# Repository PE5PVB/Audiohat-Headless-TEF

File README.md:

# Audiohat for Headless TEF

This is an add-on PCB for the Headless TEF, it will provide an extra analog audio output.

## Contributing
I'm open for a new ideas in our project. Feel free to share your thoughts in [Discussions](https://github.com/PE5PVB/Audiohat-Headless-TEF/discussions).\
You can also contribute to the project using [Pull Requests](https://github.com/PE5PVB/Audiohat-Headless-TEF/pulls). We will review it and merge into main branch.

You are using my hardware and you found a difficulty? Please create new [issue](https://github.com/PE5PVB/Audiohat-Headless-TEF/issues) and describe your problem.

I also would like to invite you to join our Discord community where we share our ideas and help each other with some issues.\

Special thanks to all [contributors](https://github.com/PE5PVB/Audiohat-Headless-TEF/graphs/contributors). You are awesome! ❤️

## If you like this hardware

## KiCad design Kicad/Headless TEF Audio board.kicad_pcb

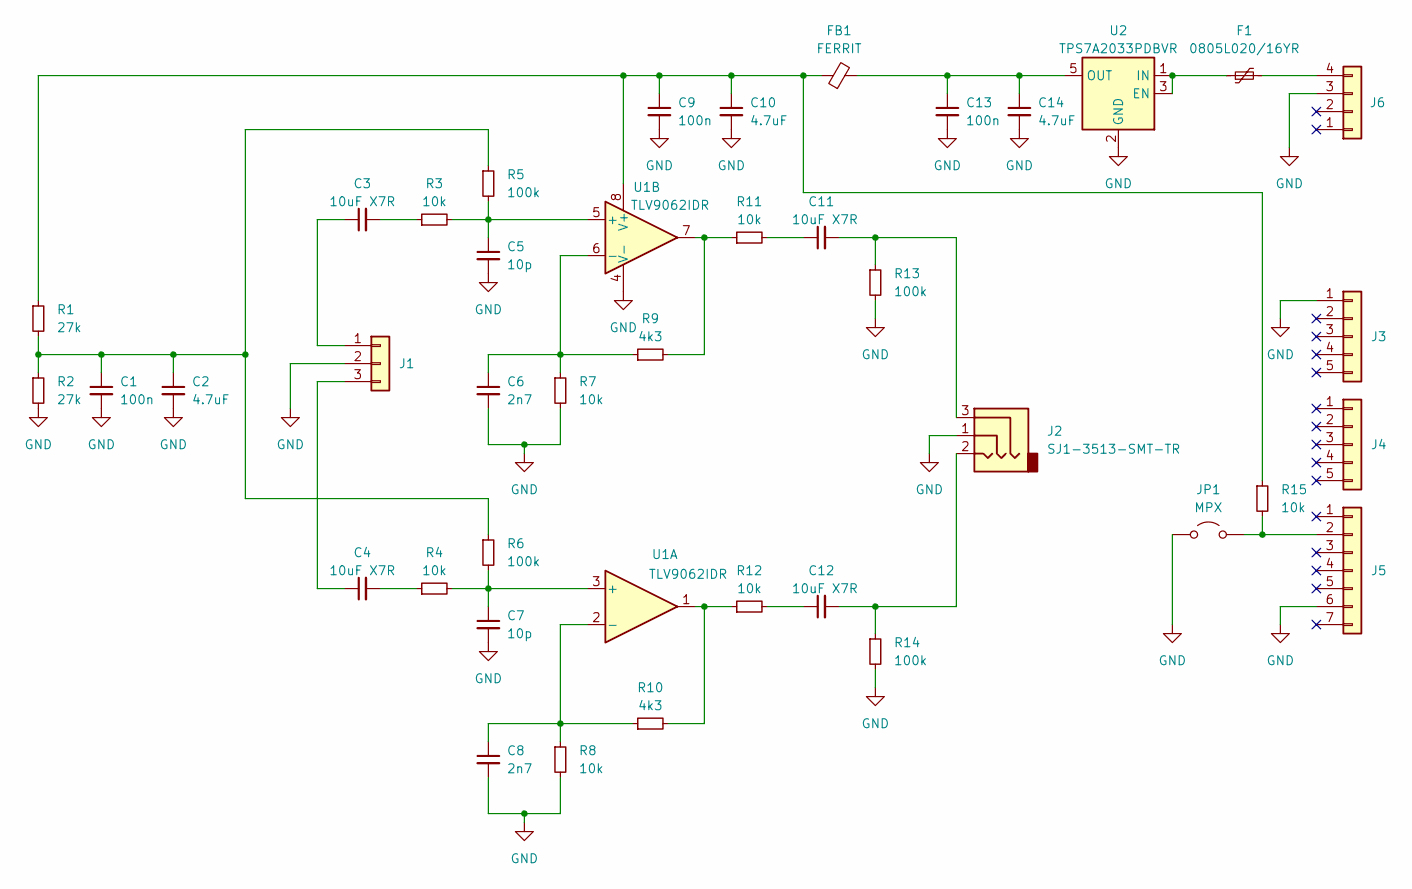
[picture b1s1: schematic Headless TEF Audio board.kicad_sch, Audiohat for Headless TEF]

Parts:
C1, C9, C13: 100n; C_0603_1608Metric
C2, C10, C14: 4.7uF; C_0603_1608Metric
C3, C4, C11, C12: 10uF X7R; C_0805_2012Metric
C5, C7: 10p; C_0603_1608Metric
C6, C8: 2n7; C_0603_1608Metric
F1: 0805L020/16YR; Fuse_0805_2012Metric
FB1: FERRIT; L_0603_1608Metric
J1: 1x3 Female; PinHeader_1x03_P2.54mm_Vertical
J2: SJ1-3513-SMT-TR; SJ1-351X-SMT
J3, J4: 1x5 Female; PinHeader_1x05_P2.54mm_Vertical
J5: 1x7 Female; PinHeader_1x07_P2.54mm_Vertical
J6: 1x4 Female; PinHeader_1x04_P2.54mm_Vertical
JP1: MPX; TestPoint_2Pads_Pitch2.54mm_Drill0.8mm
R1, R2: 27k; R_0603_1608Metric
R3, R4, R7, R8, R11, R12, R15: 10k; R_0603_1608Metric
R5, R6, R13, R14: 100k; R_0603_1608Metric
R9, R10: 4k3; R_0603_1608Metric
U1: TLV9062IDR; SOIC-8_3.9x4.9mm_P1.27mm
U2: TPS7A2033PDBVR; SOT-23-5

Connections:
GND: C1.2, C2.2, C5.2, C6.2, C7.2, C8.2, C9.2, C10.2, C13.2, C14.2, J1.2, J2.1, J3.1, J5.6, J6.3, JP1.1 (A), R2.2, R7.2, R8.2, R13.2, R14.2, U1.4 (V-), U2.2 (GND)
unnamed: C1.1, C2.1, R1.2, R2.1, R5.1, R6.1
unnamed: C3.2, R3.1
unnamed: C4.2, R4.1
unnamed: C11.1, R11.2
unnamed: C11.2, J2.3, R13.1
unnamed: C12.1, R12.2
unnamed: C12.2, J2.2, R14.1
unnamed: C3.1, J1.1
unnamed: C4.1, J1.3
unnamed: J5.2, JP1.2 (B), R15.2
unnamed: F1.2, J6.4
unnamed: R10.2, R12.1, U1.1
unnamed: R9.2, R11.1, U1.7
unnamed: C7.1, R4.2, R6.2, U1.3 (+)
unnamed: C8.1, R8.1, R10.1, U1.2 (-)
unnamed: C5.1, R3.2, R5.2, U1.5 (+)
unnamed: C6.1, R7.1, R9.1, U1.6 (-)
unnamed: C9.1, C10.1, FB1.1, R1.1, R15.1, U1.8 (V+)
unnamed: F1.1, U2.1 (IN), U2.3 (EN)
unnamed: C13.1, C14.1, FB1.2, U2.5 (OUT)

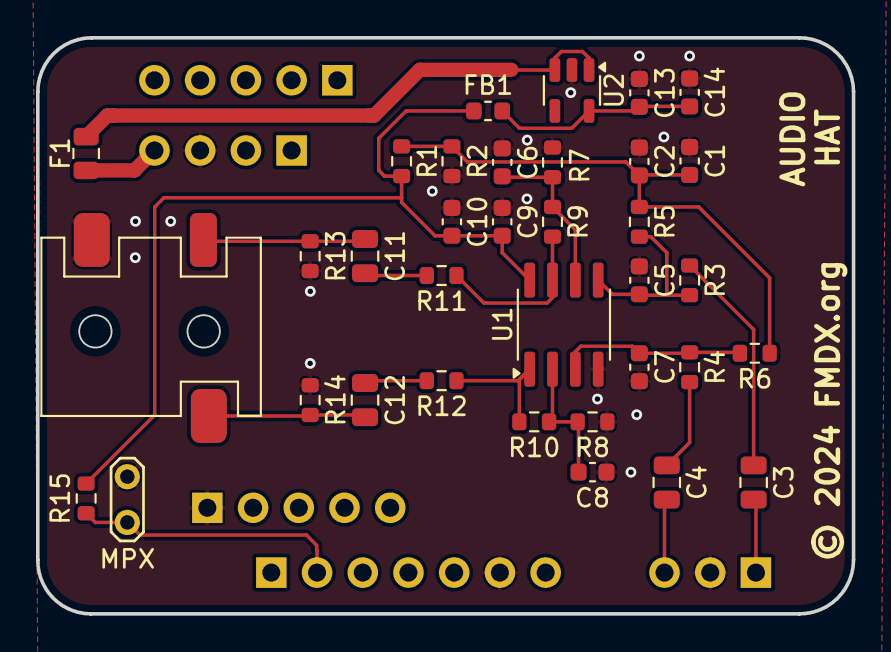
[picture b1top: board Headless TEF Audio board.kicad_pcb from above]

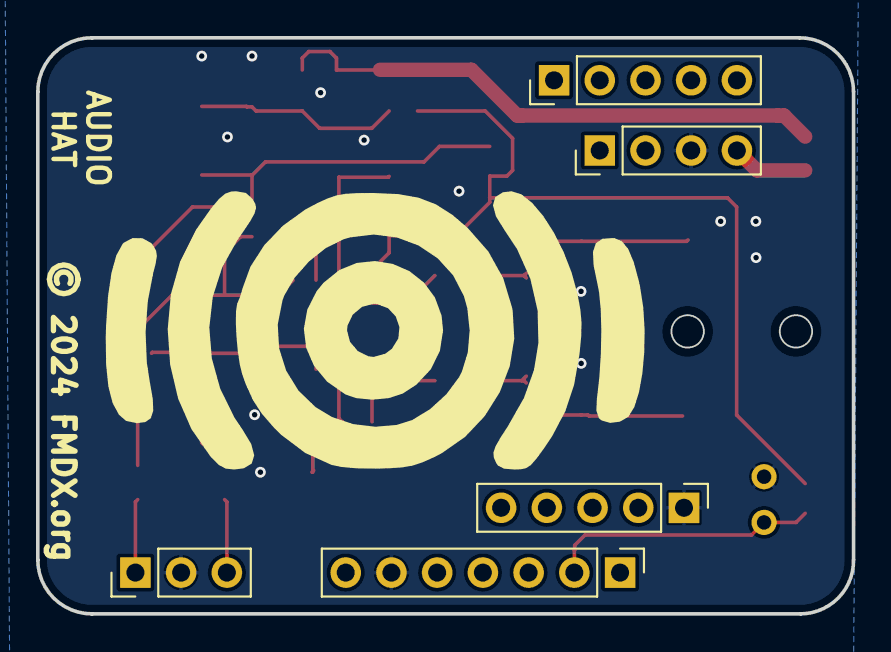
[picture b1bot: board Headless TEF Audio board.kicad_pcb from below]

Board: 2 copper layers, 45.3 x 32.0 mm, 40 parts (5 on the bottom side), 21 nets.

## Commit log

2024-08-01 Publish
2024-08-01 Optimised picture

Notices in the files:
Kicad/Headless TEF Audio board.kicad_pcb:
© 2024 FMDX.org
